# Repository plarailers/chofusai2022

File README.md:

# 調布祭 2022

開催日：2022年11月18日（金）～20日（日）

## 概要
電通大工学研究部のプラレール企画に、自動運転システムを提供する。詳細は https://scrapbox.io/plarailers-private/ueckoken%2Fplarail2022 を参照

## インストール

```sh
git clone https://github.com/plarailers/chofusai2022.git
```

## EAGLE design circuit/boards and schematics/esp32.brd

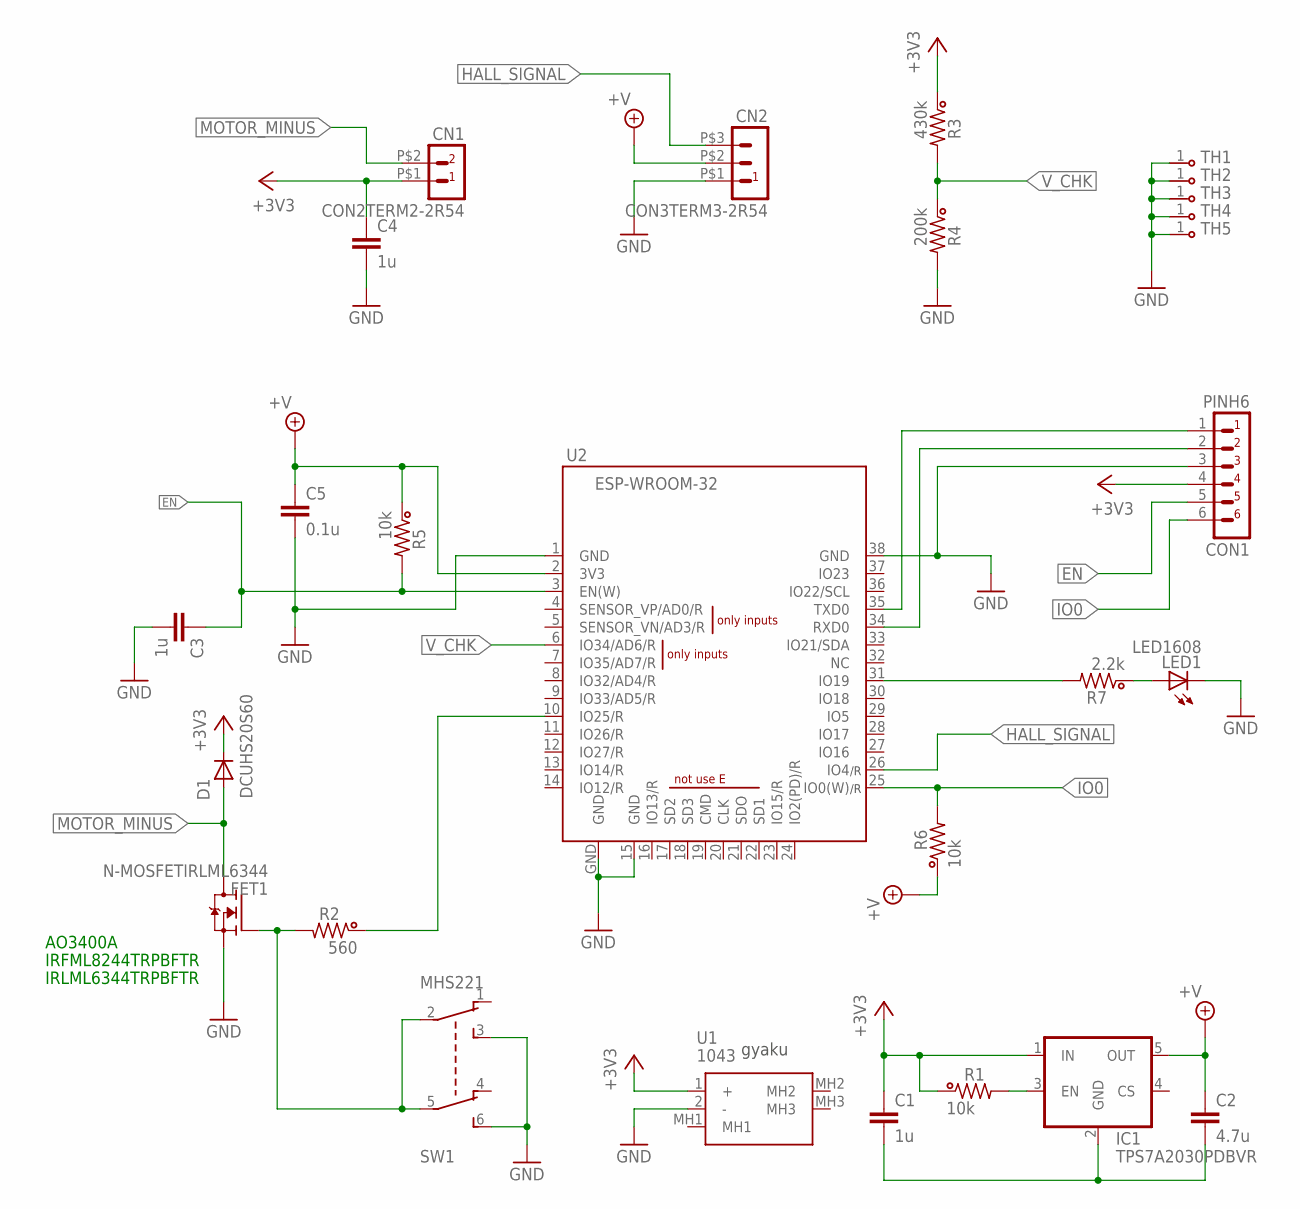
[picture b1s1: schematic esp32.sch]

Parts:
C1, C3, C4: 1u; 2015
C2: 4.7u; 2015
C5: 0.1u; 2015
CN1: CON2TERM2-2R54; TERM2-2R54
CN2: CON3TERM3-2R54; TERM3-2R54
CON1: PINH6
D1: DCUHS20S60; US2H
FET1: N-MOSFETIRLML6344; SOT23-3
IC1: TPS7A2030PDBVR; SOT23-5
LED1: LED1608
R1, R5, R6: 10k; 1608
R2: 560; 1608
R3: 430k; 1608
R4: 200k; 1608
R7: 2.2k; 1608
SW1: MHS221
TH1, TH2, TH3, TH4: THTH220; TH220
TH5: THGG; TH6-GG
U1: 1043
U2: ESP-WROOM-32

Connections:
+3V3: C1.1, C4.1, CN1.P$1 (1), CON1.4, D1.C, IC1.1 (IN), R1.1, R3.1, U1.1 (+)
+V: C2.1, C5.1, CN2.P$2 (2), IC1.5 (OUT), R5.1, R6.1, U2.2 (3V3)
EN: C3.1, CON1.5, R5.2, U2.3 (EN(W))
GND: C1.2, C2.2, C3.2, C4.2, C5.2, CN2.P$1 (1), CON1.3, FET1.2 (S), IC1.2 (GND), LED1.K (C), R4.2, SW1.3, SW1.6, TH1.1, TH2.1, TH3.1, TH4.1, TH5.1, U1.2 (-), U2.1 (GND), U2.15 (GND), U2.38 (GND), U2.GND
HALL_SIGNAL: CN2.P$3 (3), U2.26 (IO4)
IO0: CON1.6, R6.2, U2.25 (IO0(W))
MOTOR_MINUS: CN1.P$2 (2), D1.A, FET1.3 (D)
unnamed: IC1.3 (EN), R1.2
unnamed: R7.2, U2.31 (IO19)
unnamed: R2.1, U2.10 (IO25/R)
unnamed: FET1.1 (G), R2.2, SW1.2, SW1.5
unnamed: LED1.A, R7.1
V_CHK: R3.2, R4.1, U2.6 (IO34/AD6/R)
WRX: CON1.2, U2.34 (RXD0)
WTX: CON1.1, U2.35 (TXD0)

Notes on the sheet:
AO3400A
IRFML8244TRPBFTR
IRLML6344TRPBFTR
gyaku

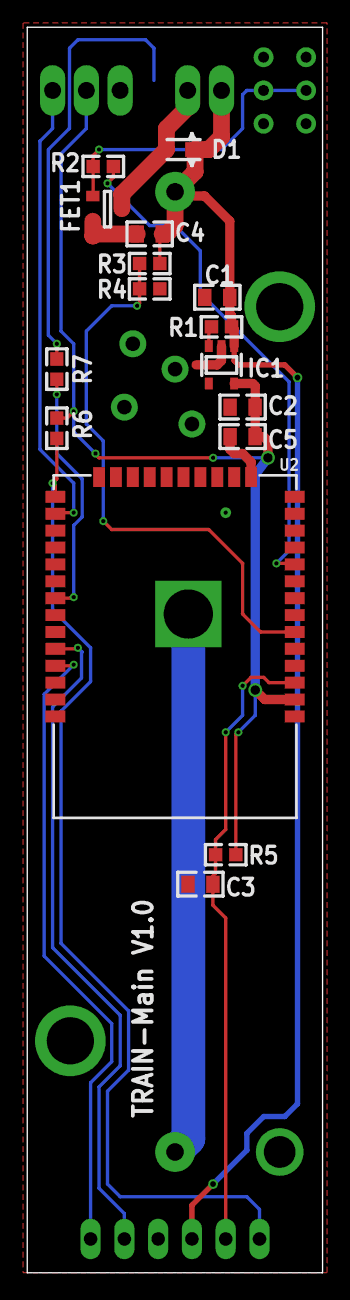
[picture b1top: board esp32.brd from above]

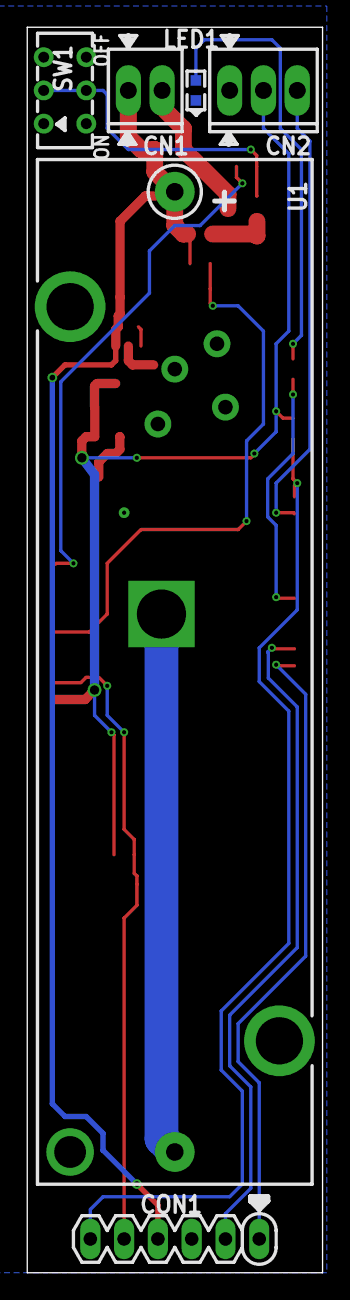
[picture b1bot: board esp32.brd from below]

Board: 2 copper layers, 22.2 x 93.7 mm, 27 parts (6 on the bottom side), 15 nets.

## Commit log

2022-11-05 create next app
2022-11-05 路線図を配置
2022-11-05 README.md を更新
2022-11-05 動いたような気もするがvisualizerで確認したいので一旦コミット
2022-11-05 send blocks by websocket
2022-11-05 comment out debug print
2022-11-05 自動運転プログラムのビジュアライザからのアクセスを許可
2022-11-05 自動運転プログラムの状態をビジュアライザに反映
2022-11-05 色を変更
2022-11-05 フォルダ構造を整理
